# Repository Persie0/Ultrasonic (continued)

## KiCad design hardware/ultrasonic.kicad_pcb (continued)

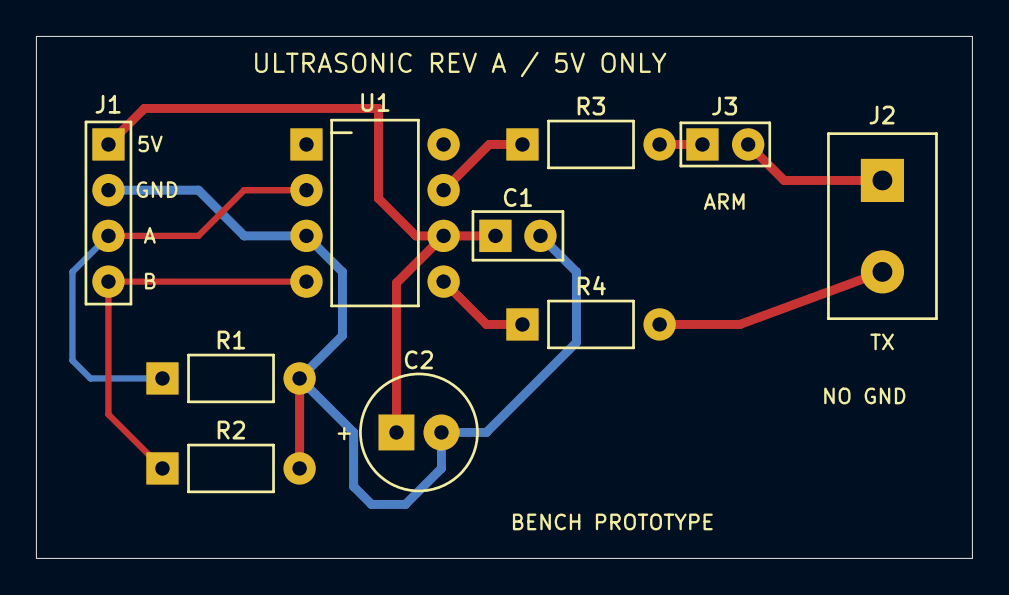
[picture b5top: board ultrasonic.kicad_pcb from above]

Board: 2 copper layers, 52.0 x 29.0 mm, 10 parts (0 on the bottom side), 9 nets.
